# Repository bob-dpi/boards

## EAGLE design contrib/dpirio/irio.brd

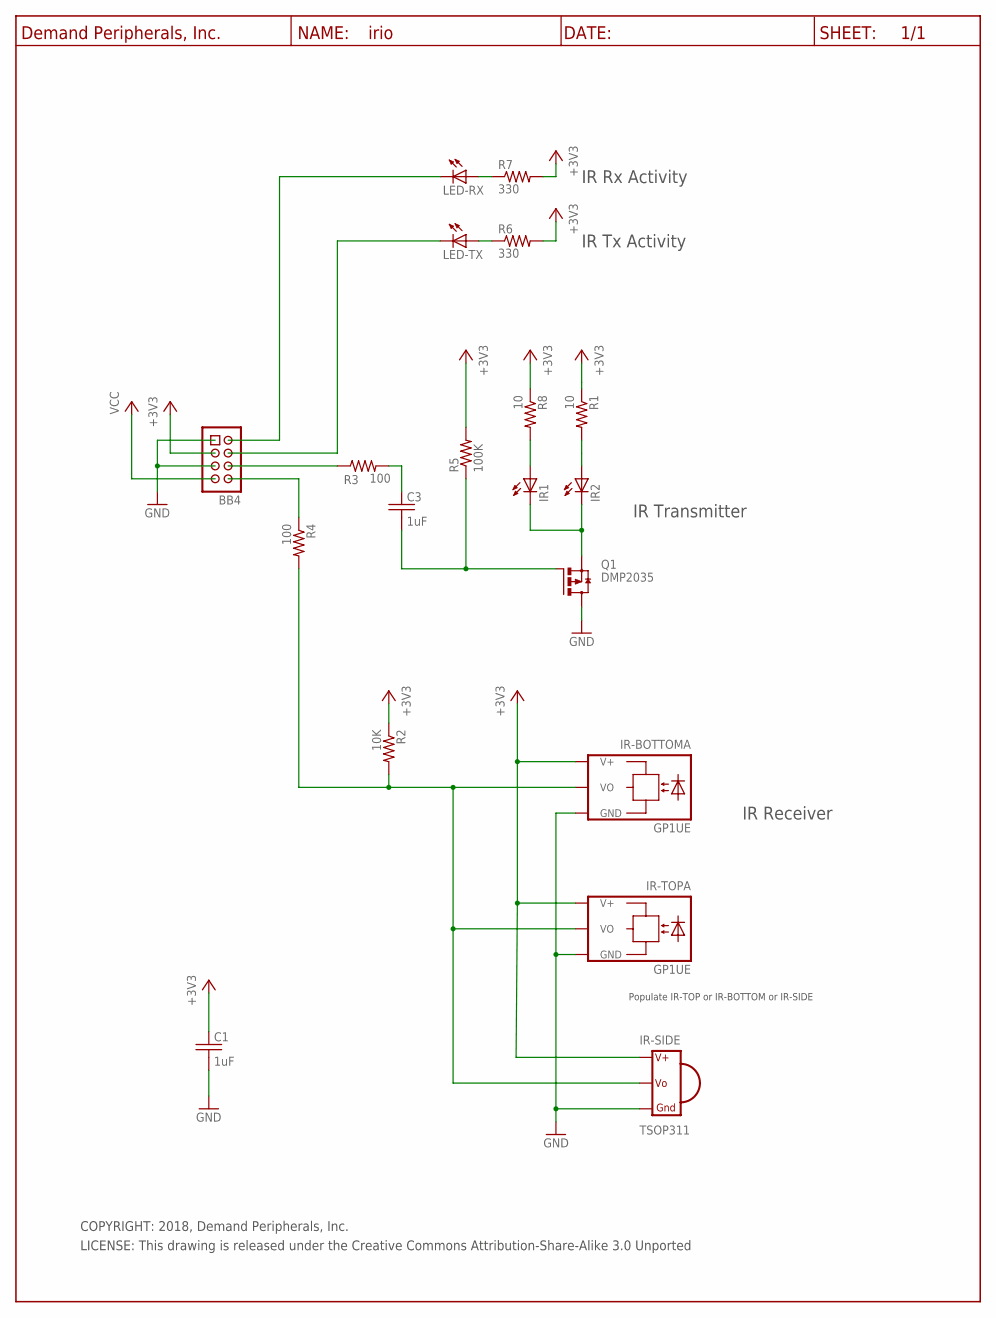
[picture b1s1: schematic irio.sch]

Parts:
BB4: BB4-CON; HDR-4X2
C1, C3: 1uF; C0603
IR1, IR2: LED-5MM-IR; LED5MM
IR-BOTTOM: GP1UE
IR-SIDE: TSOP311; TSOP-IR-SIDE
IR-TOP: GP1UE
LED-RX: LED; LED5MM
LED-TX: LED; LED5MM
Q1: DMP2035; SOT23
R1, R8: 10; R0603
R2: 10K; R0603
R3, R4: 100; R0603
R5: 100K; R0603
R6, R7: 330; R0603
U$1: DP_FRAME_P; P_FRAME

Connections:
+3V3: BB4.3, C1.1, IR-BOTTOM.2 (V+), IR-SIDE.2 (V+), IR-TOP.2 (V+), R1.1, R2.1, R5.2, R6.2, R7.2, R8.1
GND: BB4.1, BB4.5, C1.2, IR-BOTTOM.3 (GND), IR-SIDE.3 (GND), IR-TOP.3 (GND), Q1.3 (D)
IRRX-DATA: IR-BOTTOM.1 (VO), IR-SIDE.1 (VO), IR-TOP.1 (VO), R2.2, R4.2
unnamed: C3.1, R3.2
unnamed: BB4.2, LED-RX.C
unnamed: BB4.4, LED-TX.C
unnamed: BB4.6, R3.1
unnamed: BB4.8, R4.1
unnamed: IR1.A, R8.2
unnamed: C3.2, Q1.1 (G), R5.1
unnamed: IR2.A, R1.2
unnamed: IR1.C, IR2.C, Q1.2 (S)
unnamed: LED-RX.A, R7.1
unnamed: LED-TX.A, R6.1
VCC: BB4.7

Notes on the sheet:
IR Receiver
IR Tx Activity
Populate IR-TOP or IR-BOTTOM or IR-SIDE
IR Rx Activity
IR Transmitter
COPYRIGHT: 2018, Demand Peripherals, Inc.
LICENSE: This drawing is released under the Creative Commons Attribution-Share-Alike 3.0 Unported

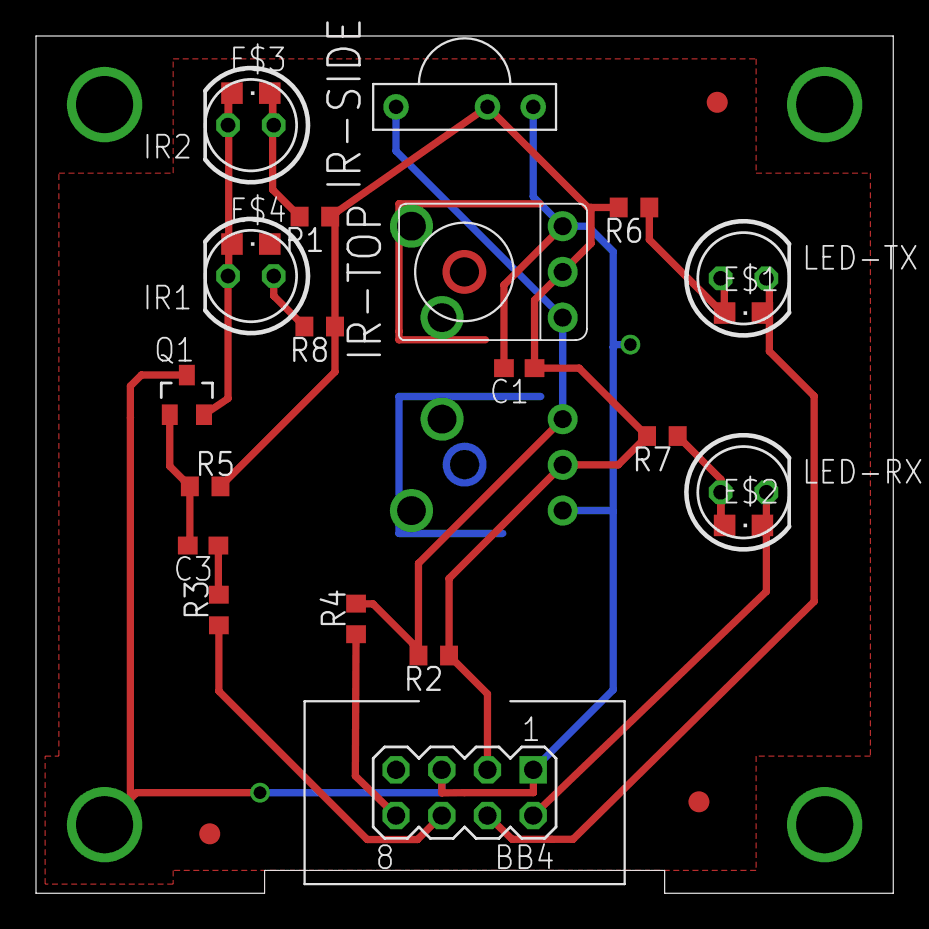
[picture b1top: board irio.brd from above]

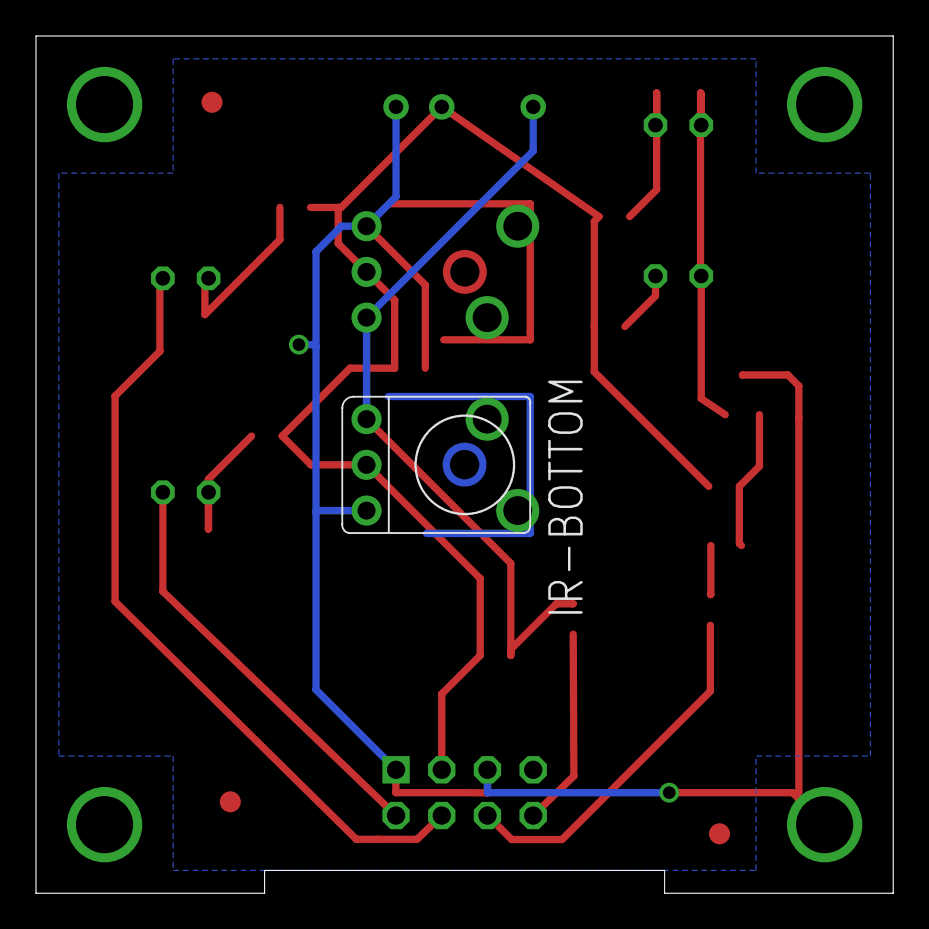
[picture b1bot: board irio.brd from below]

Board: 2 copper layers, 47.6 x 47.6 mm, 28 parts (2 on the bottom side), 14 nets.

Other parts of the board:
E$1, E$2, E$3, E$4: CHIPLED_0805
U$2: DPI-2
U$4, U$5, U$6: FIDUCIAL

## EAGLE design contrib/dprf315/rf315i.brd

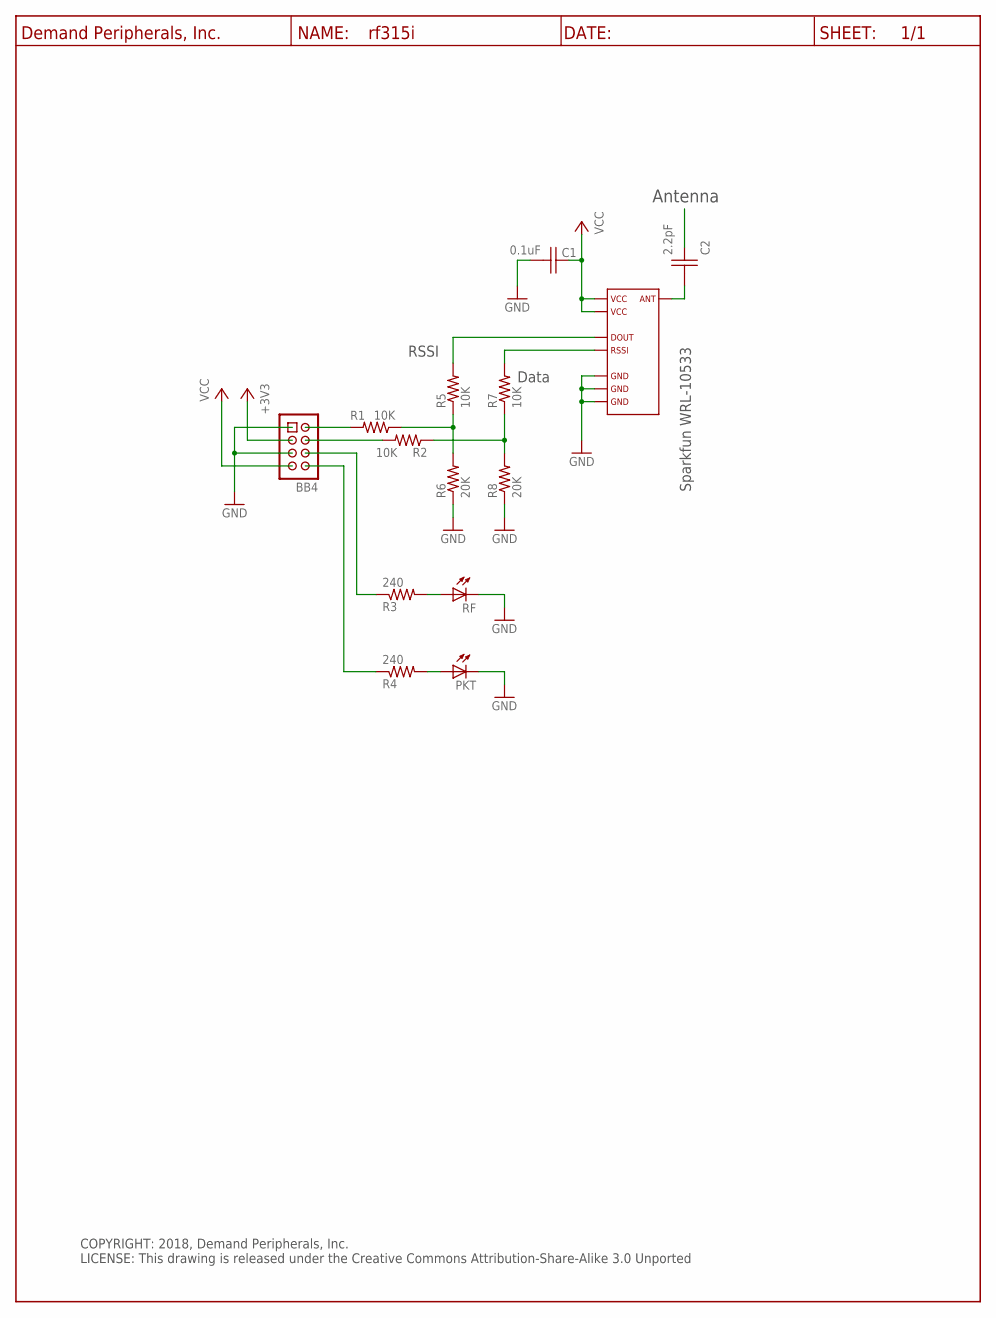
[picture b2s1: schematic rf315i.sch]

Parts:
BB4: Keyed_Pin_Header_4x2(0.1"x0.1"); HDR-4X2
C1: 0.1uF; C0603
C2: 2.2pF; C0603
PKT: LED-0805-RED; 0805
R1, R2, R5, R7: 10K; R0603
R3, R4: 240; R0603
R6, R8: 20K; R0603
RF: LED-0805-GRN; 0805
RF1: WRL-10533; RFLINK
U$1: DP_FRAME_P; P_FRAME

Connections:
+3V3: BB4.3
GND: BB4.1, BB4.5, C1.2, PKT.C, R6.1, R8.1, RF.C, RF1.1 (GND1), RF1.6 (GND3), RF1.7 (GND2)
unnamed: R3.2, RF.A
unnamed: BB4.6, R3.1
unnamed: R7.2, RF1.3 (RSSI)
unnamed: R2.1, R7.1, R8.2
unnamed: R1.1, R5.1, R6.2
unnamed: R5.2, RF1.2 (DOUT)
unnamed: BB4.8, R4.1
unnamed: PKT.A, R4.2
unnamed: BB4.2, R1.2
unnamed: BB4.4, R2.2
unnamed: C2.2, RF1.8 (ANT)
VCC: BB4.7, C1.1, RF1.4 (VCC1), RF1.5 (VCC2)

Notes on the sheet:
Antenna
RSSI
Data
COPYRIGHT: 2018, Demand Peripherals, Inc. LICENSE: This drawing is released under the Creative Commons Attribution-Share-Alike 3.0 Unported
Sparkfun WRL-10533

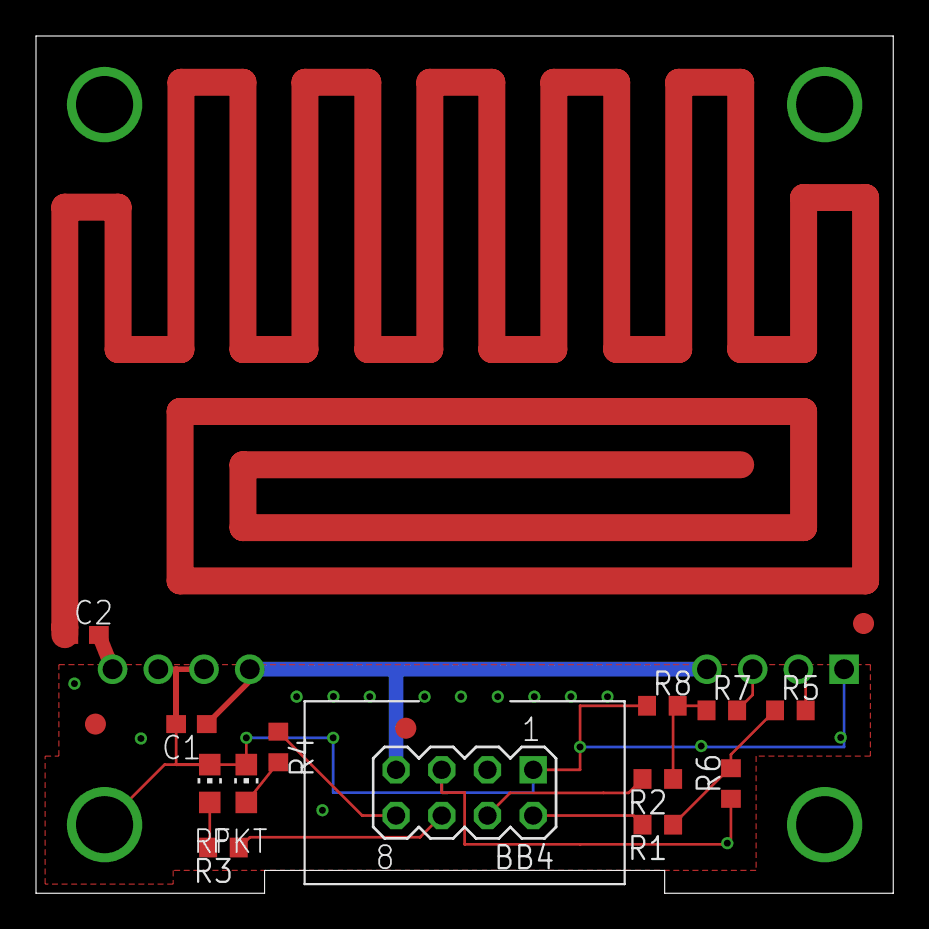
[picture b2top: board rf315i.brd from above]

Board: 2 copper layers, 47.6 x 47.6 mm, 19 parts (1 on the bottom side), 13 nets.

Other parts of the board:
U$2, U$3, U$4: FIDUCIAL
U$5: DPI-2

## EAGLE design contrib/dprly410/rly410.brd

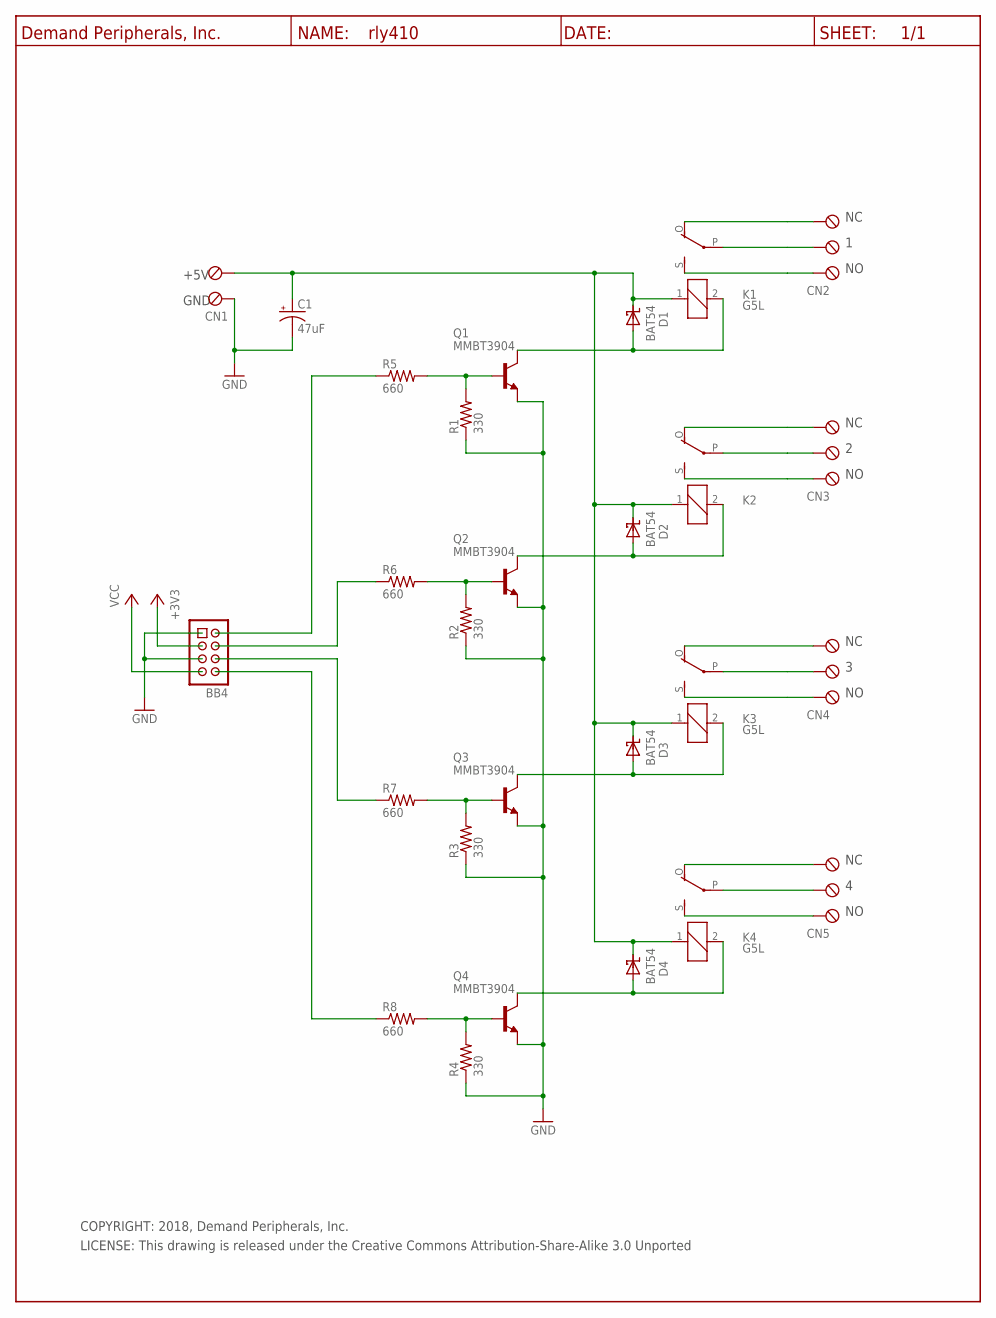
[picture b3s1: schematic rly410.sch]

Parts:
BB4: Keyed_Pin_Header_4x2(0.1"x0.1"); HDR-4X2
C1: 47uF; E3.5-8
CN1: TBLK-5.08-X2
CN2, CN3, CN4, CN5: TBLK-5.08-X3
D1, D2, D3, D4: BAT54; SOT23
K1, K2, K3, K4: G5L; G5LE
Q1, Q2, Q3, Q4: MMBT3904; SOT23
R1, R2, R3, R4: 330; R0603
R5, R6, R7, R8: 660; R0603
U$1: DP_FRAME_P; P_FRAME

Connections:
+3V3: BB4.3
GND: BB4.1, BB4.5, C1.-, CN1.1 (KL), Q1.2 (E), Q2.2 (E), Q3.2 (E), Q4.2 (E), R1.1, R2.1, R3.1, R4.1
unnamed: CN4.3 (KL2), K3.O
unnamed: BB4.2, R5.1
unnamed: CN5.1 (KL), K4.S
unnamed: BB4.4, R6.1
unnamed: BB4.6, R7.1
unnamed: Q4.1 (B), R4.2, R8.2
unnamed: C1.+, CN1.2 (KL1), D1.3 (CC), D2.3 (CC), D3.3 (CC), D4.3 (CC), K1.1, K2.1, K3.1, K4.1
unnamed: Q3.1 (B), R3.2, R7.2
unnamed: D1.1 (A), K1.2, Q1.3 (C)
unnamed: D2.1 (A), K2.2, Q2.3 (C)
unnamed: D3.1 (A), K3.2, Q3.3 (C)
unnamed: D4.1 (A), K4.2, Q4.3 (C)
unnamed: Q2.1 (B), R2.2, R6.2
unnamed: BB4.8, R8.1
unnamed: Q1.1 (B), R1.2, R5.2
unnamed: CN5.3 (KL2), K4.O
unnamed: CN5.2 (KL1), K4.P
unnamed: CN4.2 (KL1), K3.P
unnamed: CN4.1 (KL), K3.S
unnamed: CN3.2 (KL1), K2.P
unnamed: CN3.3 (KL2), K2.O
unnamed: CN3.1 (KL), K2.S
unnamed: CN2.2 (KL1), K1.P
unnamed: CN2.3 (KL2), K1.O
unnamed: CN2.1 (KL), K1.S
VCC: BB4.7

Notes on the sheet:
+5V
GND
COPYRIGHT: 2018, Demand Peripherals, Inc.
LICENSE: This drawing is released under the Creative Commons Attribution-Share-Alike 3.0 Unported

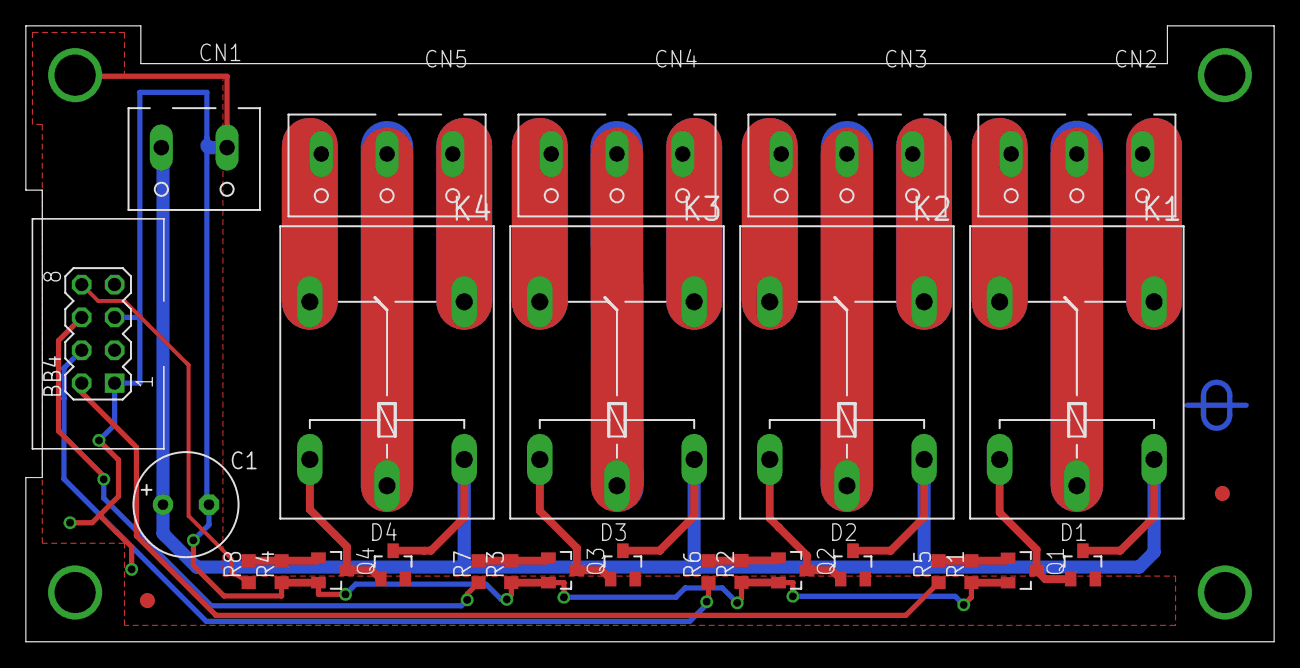
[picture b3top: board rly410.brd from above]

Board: 2 copper layers, 96.5 x 47.6 mm, 31 parts (1 on the bottom side), 26 nets.

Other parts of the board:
U$2: DPI-1
U$4, U$5: FIDUCIAL

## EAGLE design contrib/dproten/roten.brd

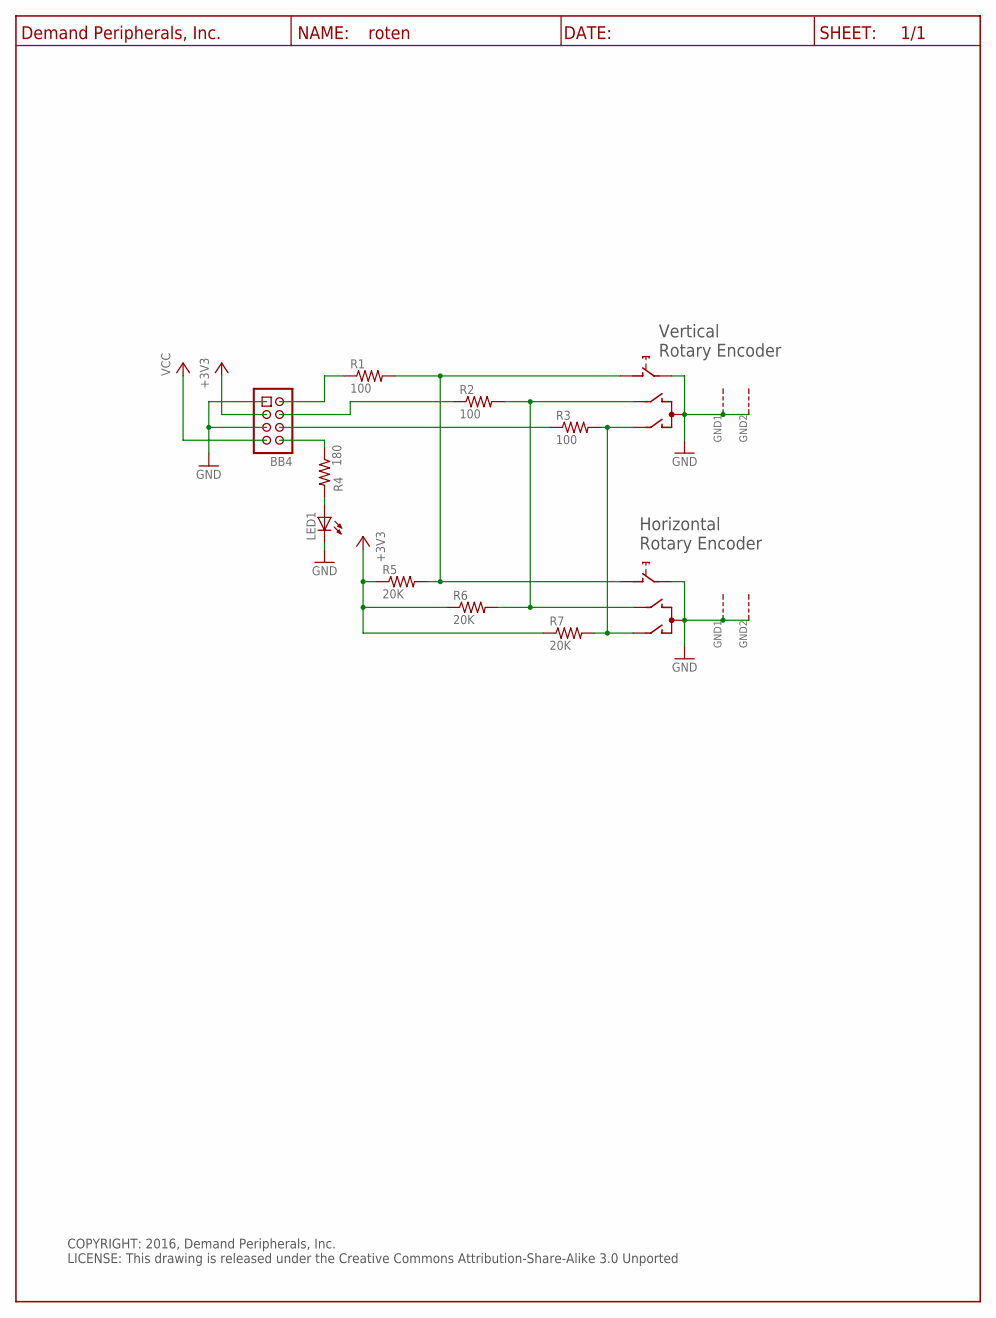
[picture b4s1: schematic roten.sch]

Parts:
1: ROTARY_ENCODER_W_SWITCHCTS_V_120; CTS_290_VERT
2: ROTARY_ENCODER_W_SWITCH; BI_EN11_HORIZ
BB4: HDR-4X2-SHR; HDR-4X2
LED1: LED-5MM-GRN; LED5MM
R1, R2, R3: 100; R0603
R4: 180; R0603
R5, R6, R7: 20K; R0603
U$1: DP_FRAME_P; P_FRAME

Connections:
+3V3: BB4.3, R5.1, R6.1, R7.1
GND: 1.C, 1.E, 1.GND1 (G), 1.GND2 (G), 2.C, 2.E, 2.GND1 (G), 2.GND2 (G), BB4.1, BB4.5, LED1.C
unnamed: 1.D, 2.D, R1.2, R5.2
unnamed: BB4.2, R1.1
unnamed: BB4.4, R2.1
unnamed: BB4.6, R3.1
unnamed: BB4.8, R4.1
unnamed: LED1.A, R4.2
unnamed: 1.A, 2.A, R3.2, R7.2
unnamed: 1.B, 2.B, R2.2, R6.2
VCC: BB4.7

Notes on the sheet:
Vertical
Horizontal
Rotary Encoder
COPYRIGHT: 2016, Demand Peripherals, Inc. LICENSE: This drawing is released under the Creative Commons Attribution-Share-Alike 3.0 Unported

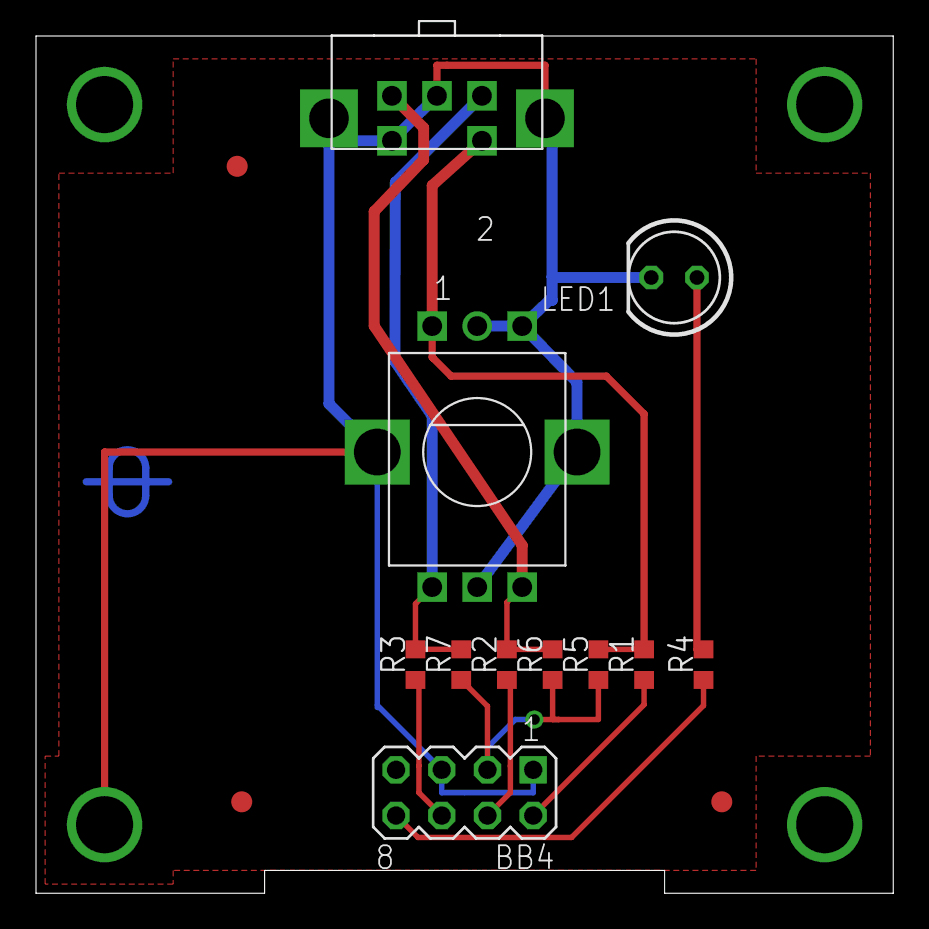
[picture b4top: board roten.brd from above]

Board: 2 copper layers, 47.6 x 47.6 mm, 16 parts (1 on the bottom side), 10 nets.

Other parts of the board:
U$4, U$5, U$6: FIDUCIAL
U$7: DPI-1

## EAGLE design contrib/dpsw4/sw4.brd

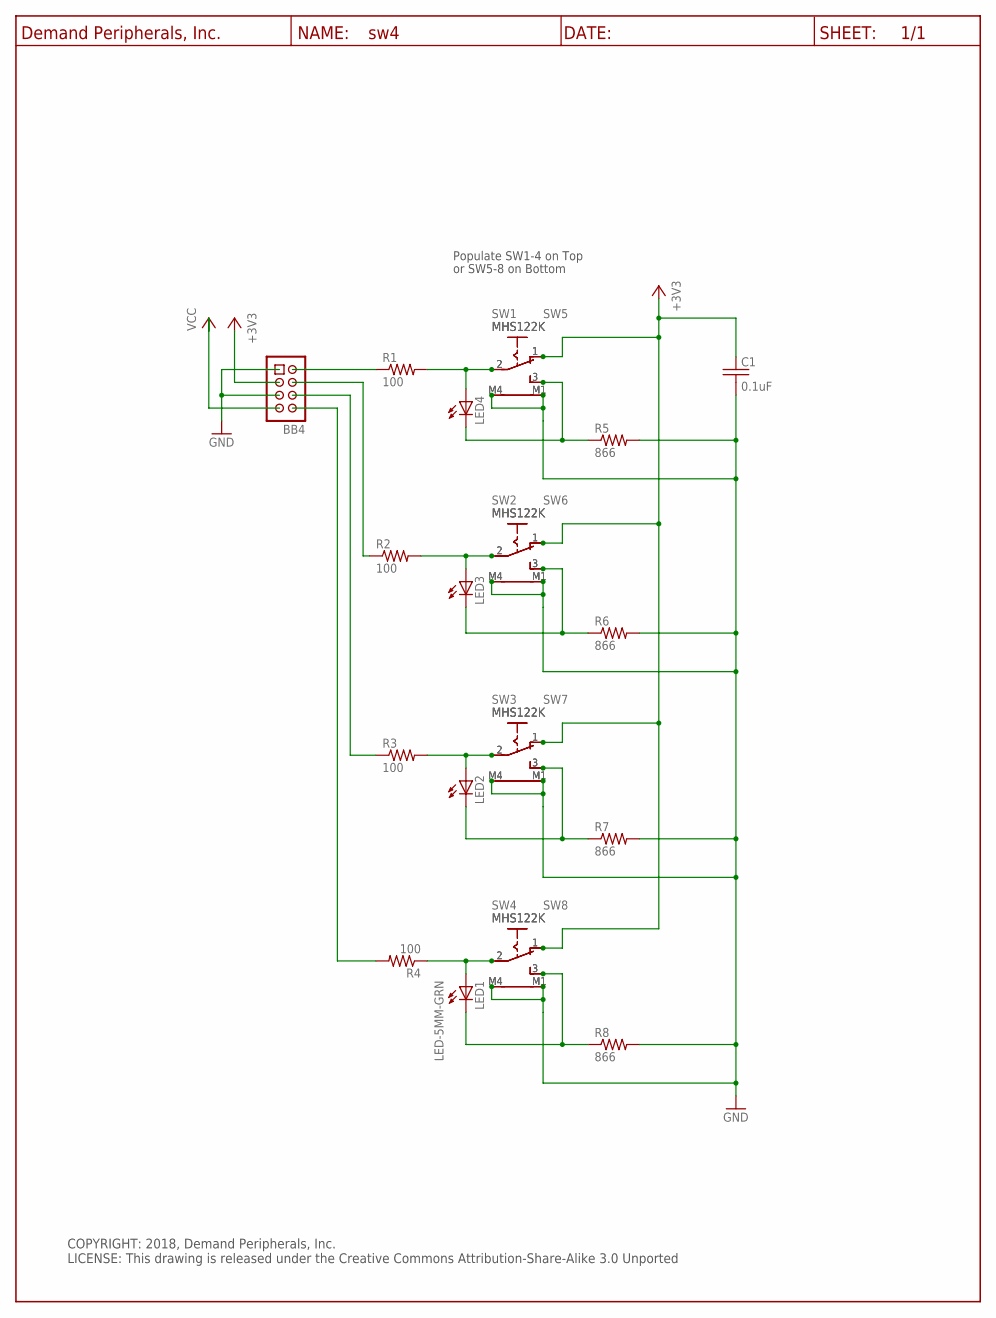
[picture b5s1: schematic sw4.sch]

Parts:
BB4: hdr4x2; HDR-4X2
C1: 0.1uF; C0603
LED1, LED2, LED3, LED4: LED-5MM-GRN; LED5MM
R1, R2, R3, R4: 100; R0603
R5, R6, R7, R8: 866; R0603
SW1, SW2, SW3, SW4, SW5, SW6, SW7, SW8: MHS122K
U$1: DP_FRAME_P; P_FRAME

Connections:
+3V3: BB4.3, C1.1, SW1.1 (O), SW2.1 (O), SW3.1 (O), SW4.1 (O), SW5.1 (O), SW6.1 (O), SW7.1 (O), SW8.1 (O)
GND: BB4.1, BB4.5, C1.2, R5.2, R6.2, R7.2, R8.2, SW1.M1 (B1), SW1.M4 (B), SW2.M1 (B1), SW2.M4 (B), SW3.M1 (B1), SW3.M4 (B), SW4.M1 (B1), SW4.M4 (B), SW5.M1 (B1), SW5.M4 (B), SW6.M1 (B1), SW6.M4 (B), SW7.M1 (B1), SW7.M4 (B), SW8.M1 (B1), SW8.M4 (B)
unnamed: BB4.8, R4.2
unnamed: LED4.C, R5.1, SW1.3 (S), SW5.3 (S)
unnamed: LED4.A, R1.2, SW1.2, SW5.2
unnamed: LED3.A, R2.2, SW2.2, SW6.2
unnamed: LED2.A, R3.2, SW3.2, SW7.2
unnamed: LED1.A, R4.1, SW4.2, SW8.2
unnamed: LED3.C, R6.1, SW2.3 (S), SW6.3 (S)
unnamed: LED2.C, R7.1, SW3.3 (S), SW7.3 (S)
unnamed: LED1.C, R8.1, SW4.3 (S), SW8.3 (S)
unnamed: BB4.2, R1.1
unnamed: BB4.6, R3.1
unnamed: BB4.4, R2.1
VCC: BB4.7

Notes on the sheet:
COPYRIGHT: 2018, Demand Peripherals, Inc. LICENSE: This drawing is released under the Creative Commons Attribution-Share-Alike 3.0 Unported
Populate SW1-4 on Top
or SW5-8 on Bottom

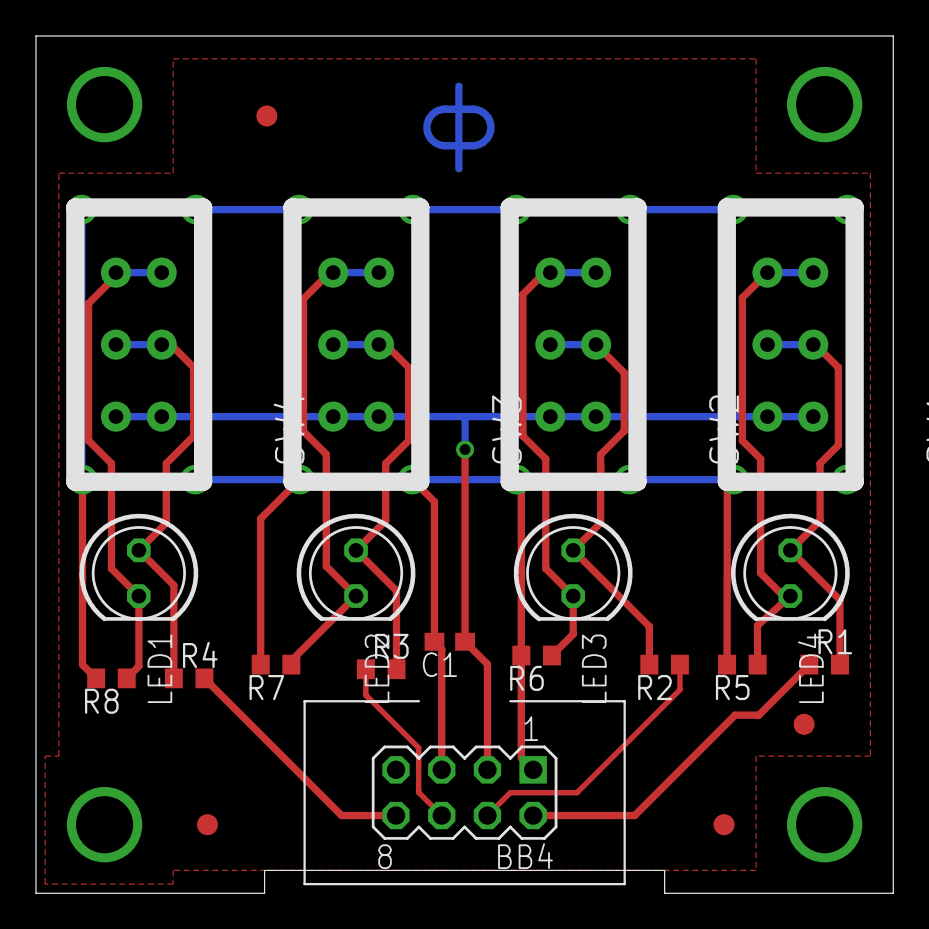
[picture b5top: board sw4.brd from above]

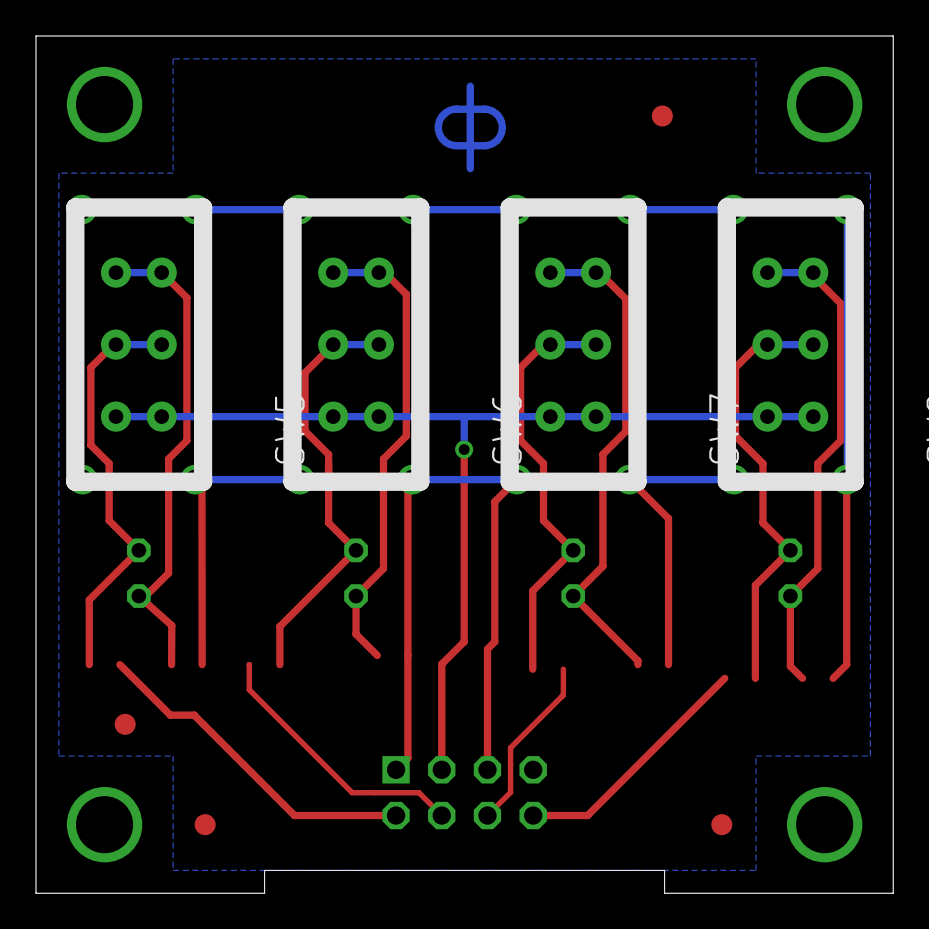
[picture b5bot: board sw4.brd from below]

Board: 2 copper layers, 47.6 x 47.6 mm, 28 parts (5 on the bottom side), 14 nets.

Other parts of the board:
U$3, U$4, U$5, U$6: FIDUCIAL
U$7: DPI-1

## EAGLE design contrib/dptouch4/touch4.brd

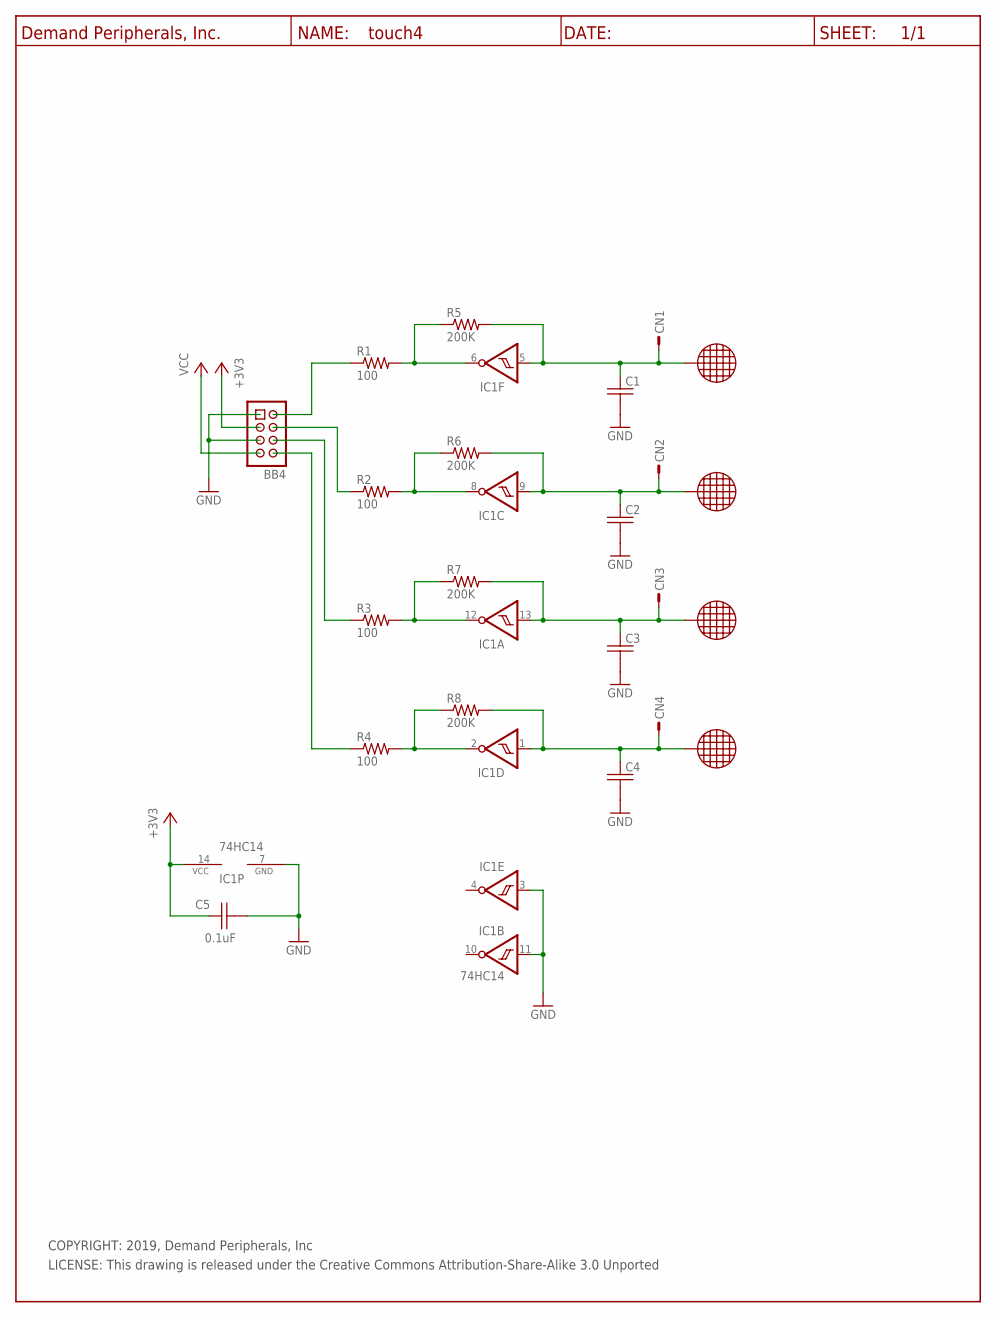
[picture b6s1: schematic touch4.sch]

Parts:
BB4: BB_CON; HDR-4X2
C1, C2, C3, C4: C33PF_C0603; C0603
C5: 0.1uF; C0603
CN1, CN2, CN3, CN4: PAD1
IC1: 74HC14; SO14
R1, R2, R3, R4: 100; R0603
R5, R6, R7, R8: 200K; R0603
U$1: DP_FRAME_P; P_FRAME
U$5, U$6, U$7, U$9: TOUCH-9MM

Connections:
+3V3: BB4.3, C5.1, IC1.14 (VCC)
GND: BB4.1, BB4.5, C1.2, C2.2, C3.2, C4.2, C5.2, IC1.3 (I), IC1.7 (GND), IC1.11 (I)
unnamed: C3.1, CN3.1, IC1.13 (I), R7.2, U$7.1
unnamed: BB4.8, R4.1
unnamed: BB4.2, R1.1
unnamed: BB4.4, R2.1
unnamed: BB4.6, R3.1
unnamed: IC1.6 (O), R1.2, R5.1
unnamed: IC1.8 (O), R2.2, R6.1
unnamed: IC1.12 (O), R3.2, R7.1
unnamed: IC1.2 (O), R4.2, R8.1
unnamed: C4.1, CN4.1, IC1.1 (I), R8.2, U$9.1
unnamed: C1.1, CN1.1, IC1.5 (I), R5.2, U$5.1
unnamed: C2.1, CN2.1, IC1.9 (I), R6.2, U$6.1
VCC: BB4.7

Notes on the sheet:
COPYRIGHT: 2019, Demand Peripherals, Inc
LICENSE: This drawing is released under the Creative Commons Attribution-Share-Alike 3.0 Unported

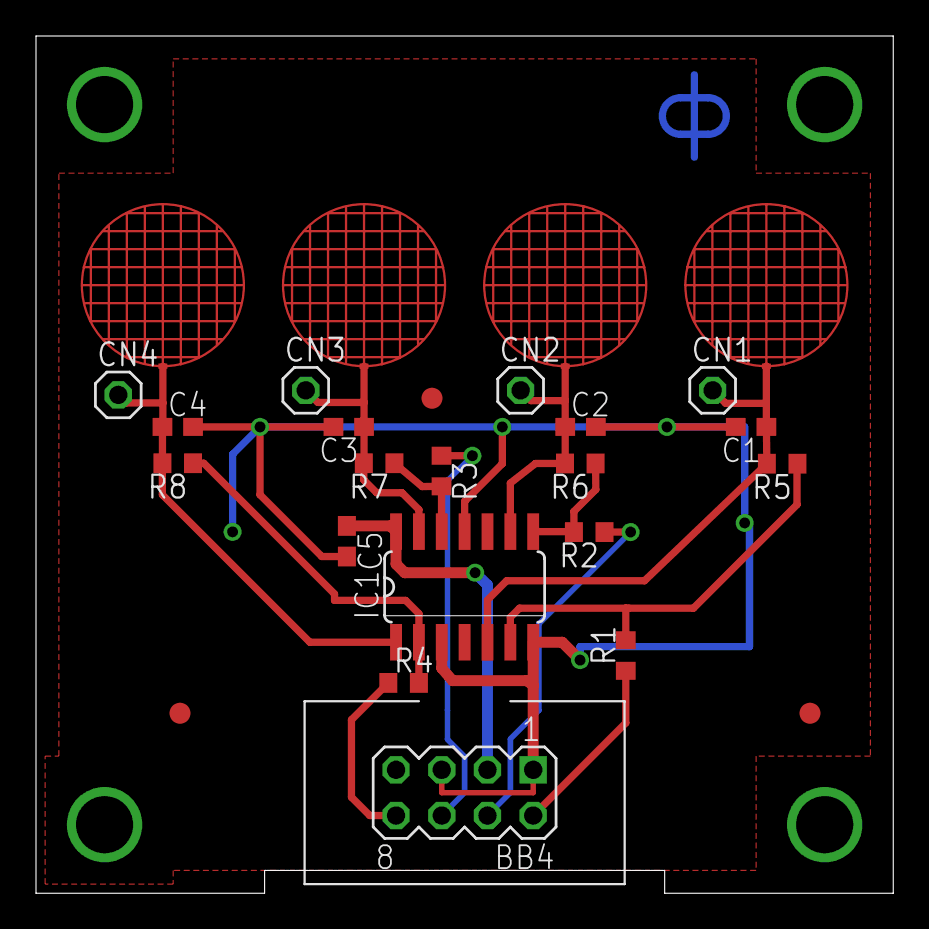
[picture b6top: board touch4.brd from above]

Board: 2 copper layers, 47.6 x 47.6 mm, 28 parts (1 on the bottom side), 14 nets.

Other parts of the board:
U$2, U$3, U$8: FIDUCIAL
U$4: DPI-1

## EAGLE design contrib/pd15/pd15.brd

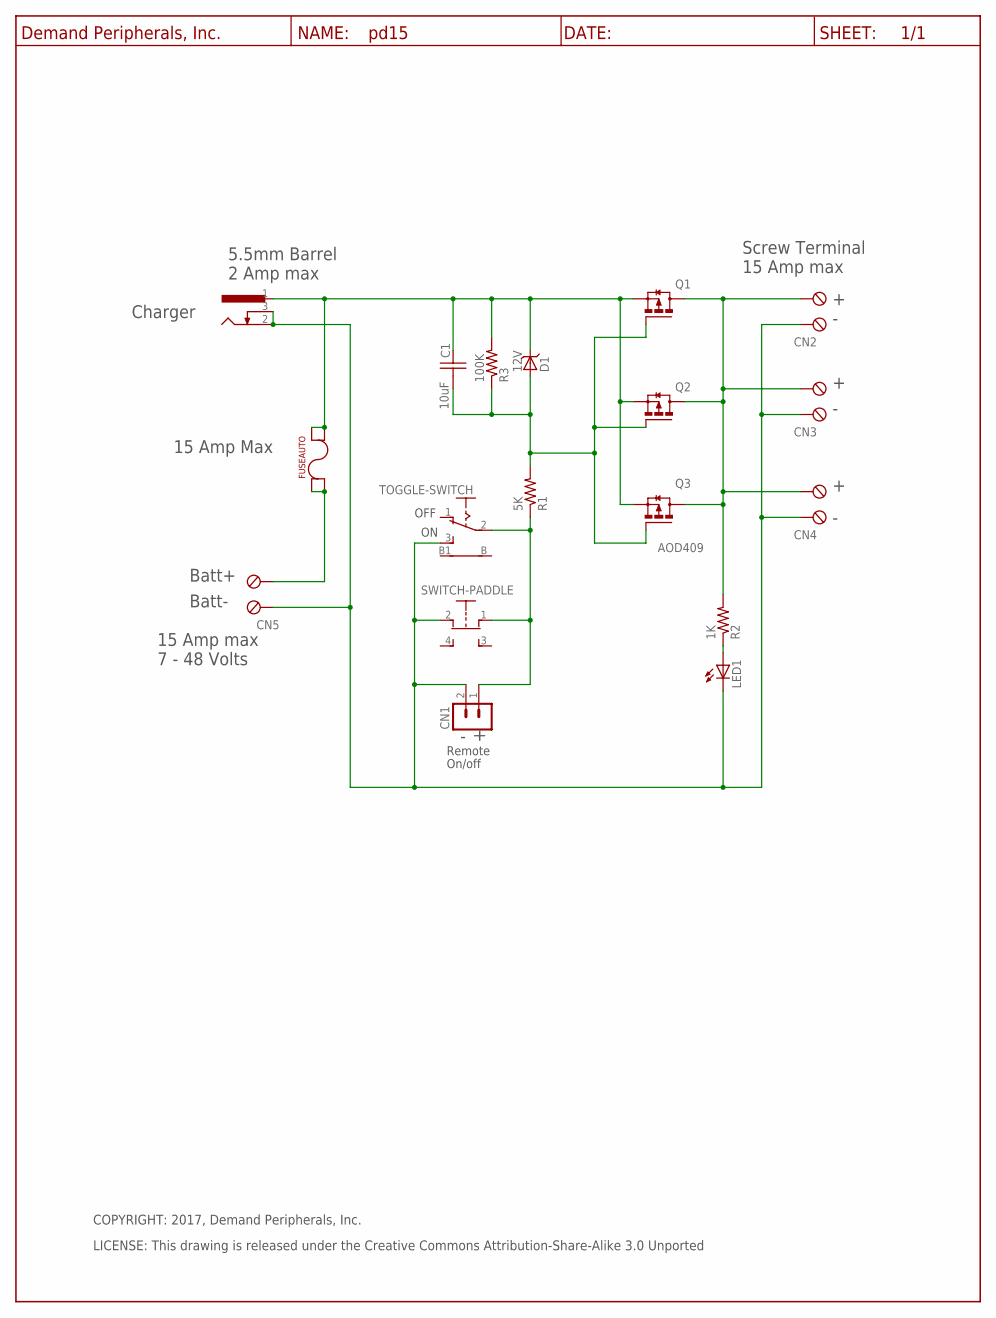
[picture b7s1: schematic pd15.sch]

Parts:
C1: 10uF; C0805
CN1: HDR-2X1-LCK; HDR-2X1
CN2, CN3, CN4, CN5: TBLK-5.08-X2
D1: 12V; SOD123
FUSE: FUSEAUTO; KS3557-10
J1: Barrel-5.5mm; DC-BARREL-JACK-55MM
LED1: LED-5MM-GRN; LED5MM
Q1, Q2: FET_DPAK_P; DPACK_TO-252
Q3: AOD409; DPACK_TO-252
R1: 5K; R0603
R2: 1K; R0603
R3: 100K; R0603
SW2: SWITCH-PADDLE
TOGGLE-SWITCH: B12EH; TOGGLE_SPDT_PC
U$1: DP_FRAME_P; LETTER_P

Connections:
BATT+: CN5.2 (KL1), FUSE.LS@1 (LS), FUSE.LS@2 (LS)
FUSE+: C1.1, D1.C, FUSE.RS@3 (RS), FUSE.RS@4 (RS), J1.1, Q1.3 (S), Q2.3 (S), Q3.3 (S), R3.2
GND: CN1.2 (1), CN2.1 (KL), CN3.1 (KL), CN4.1 (KL), CN5.1 (KL), J1.2, J1.3, LED1.C, SW2.2, TOGGLE-SWITCH.3 (S)
unnamed: LED1.A, R2.1
unnamed: C1.2, D1.A, Q1.1 (G), Q2.1 (G), Q3.1 (G), R1.2, R3.1
ON+: CN1.1 (2), R1.1, SW2.1, TOGGLE-SWITCH.2
V+: CN2.2 (KL1), CN3.2 (KL1), CN4.2 (KL1), Q1.4 (D), Q2.4 (D), Q3.4 (D), R2.2

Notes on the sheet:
Batt-
Batt+
Charger
OFF
Remote
On/off
15 Amp Max
7 - 48 Volts
15 Amp max
2 Amp max
5.5mm Barrel
Screw Terminal
COPYRIGHT: 2017, Demand Peripherals, Inc.
LICENSE: This drawing is released under the Creative Commons Attribution-Share-Alike 3.0 Unported

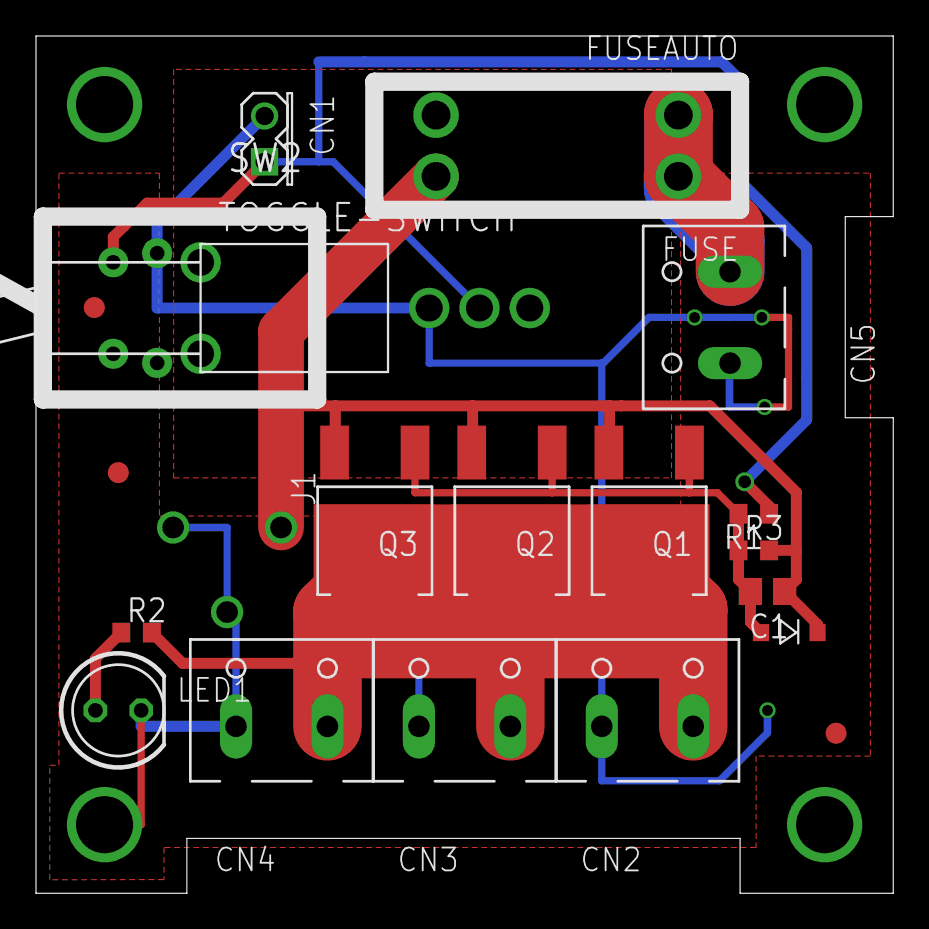
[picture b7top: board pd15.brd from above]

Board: 2 copper layers, 47.6 x 47.6 mm, 23 parts (1 on the bottom side), 7 nets.

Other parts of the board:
U$3, U$4, U$12: FIDUCIAL
U$8: DPI-2

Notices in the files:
contrib/dpirio/irio.brd:
(C) 2019, Demand Peripherals, Inc.
contrib/dprf315/rf315i.brd:
(C) 2017, Demand Peripherals, Inc.
contrib/dprly410/rly410.brd:
(C) 2018, Demand Peripherals, Inc.
